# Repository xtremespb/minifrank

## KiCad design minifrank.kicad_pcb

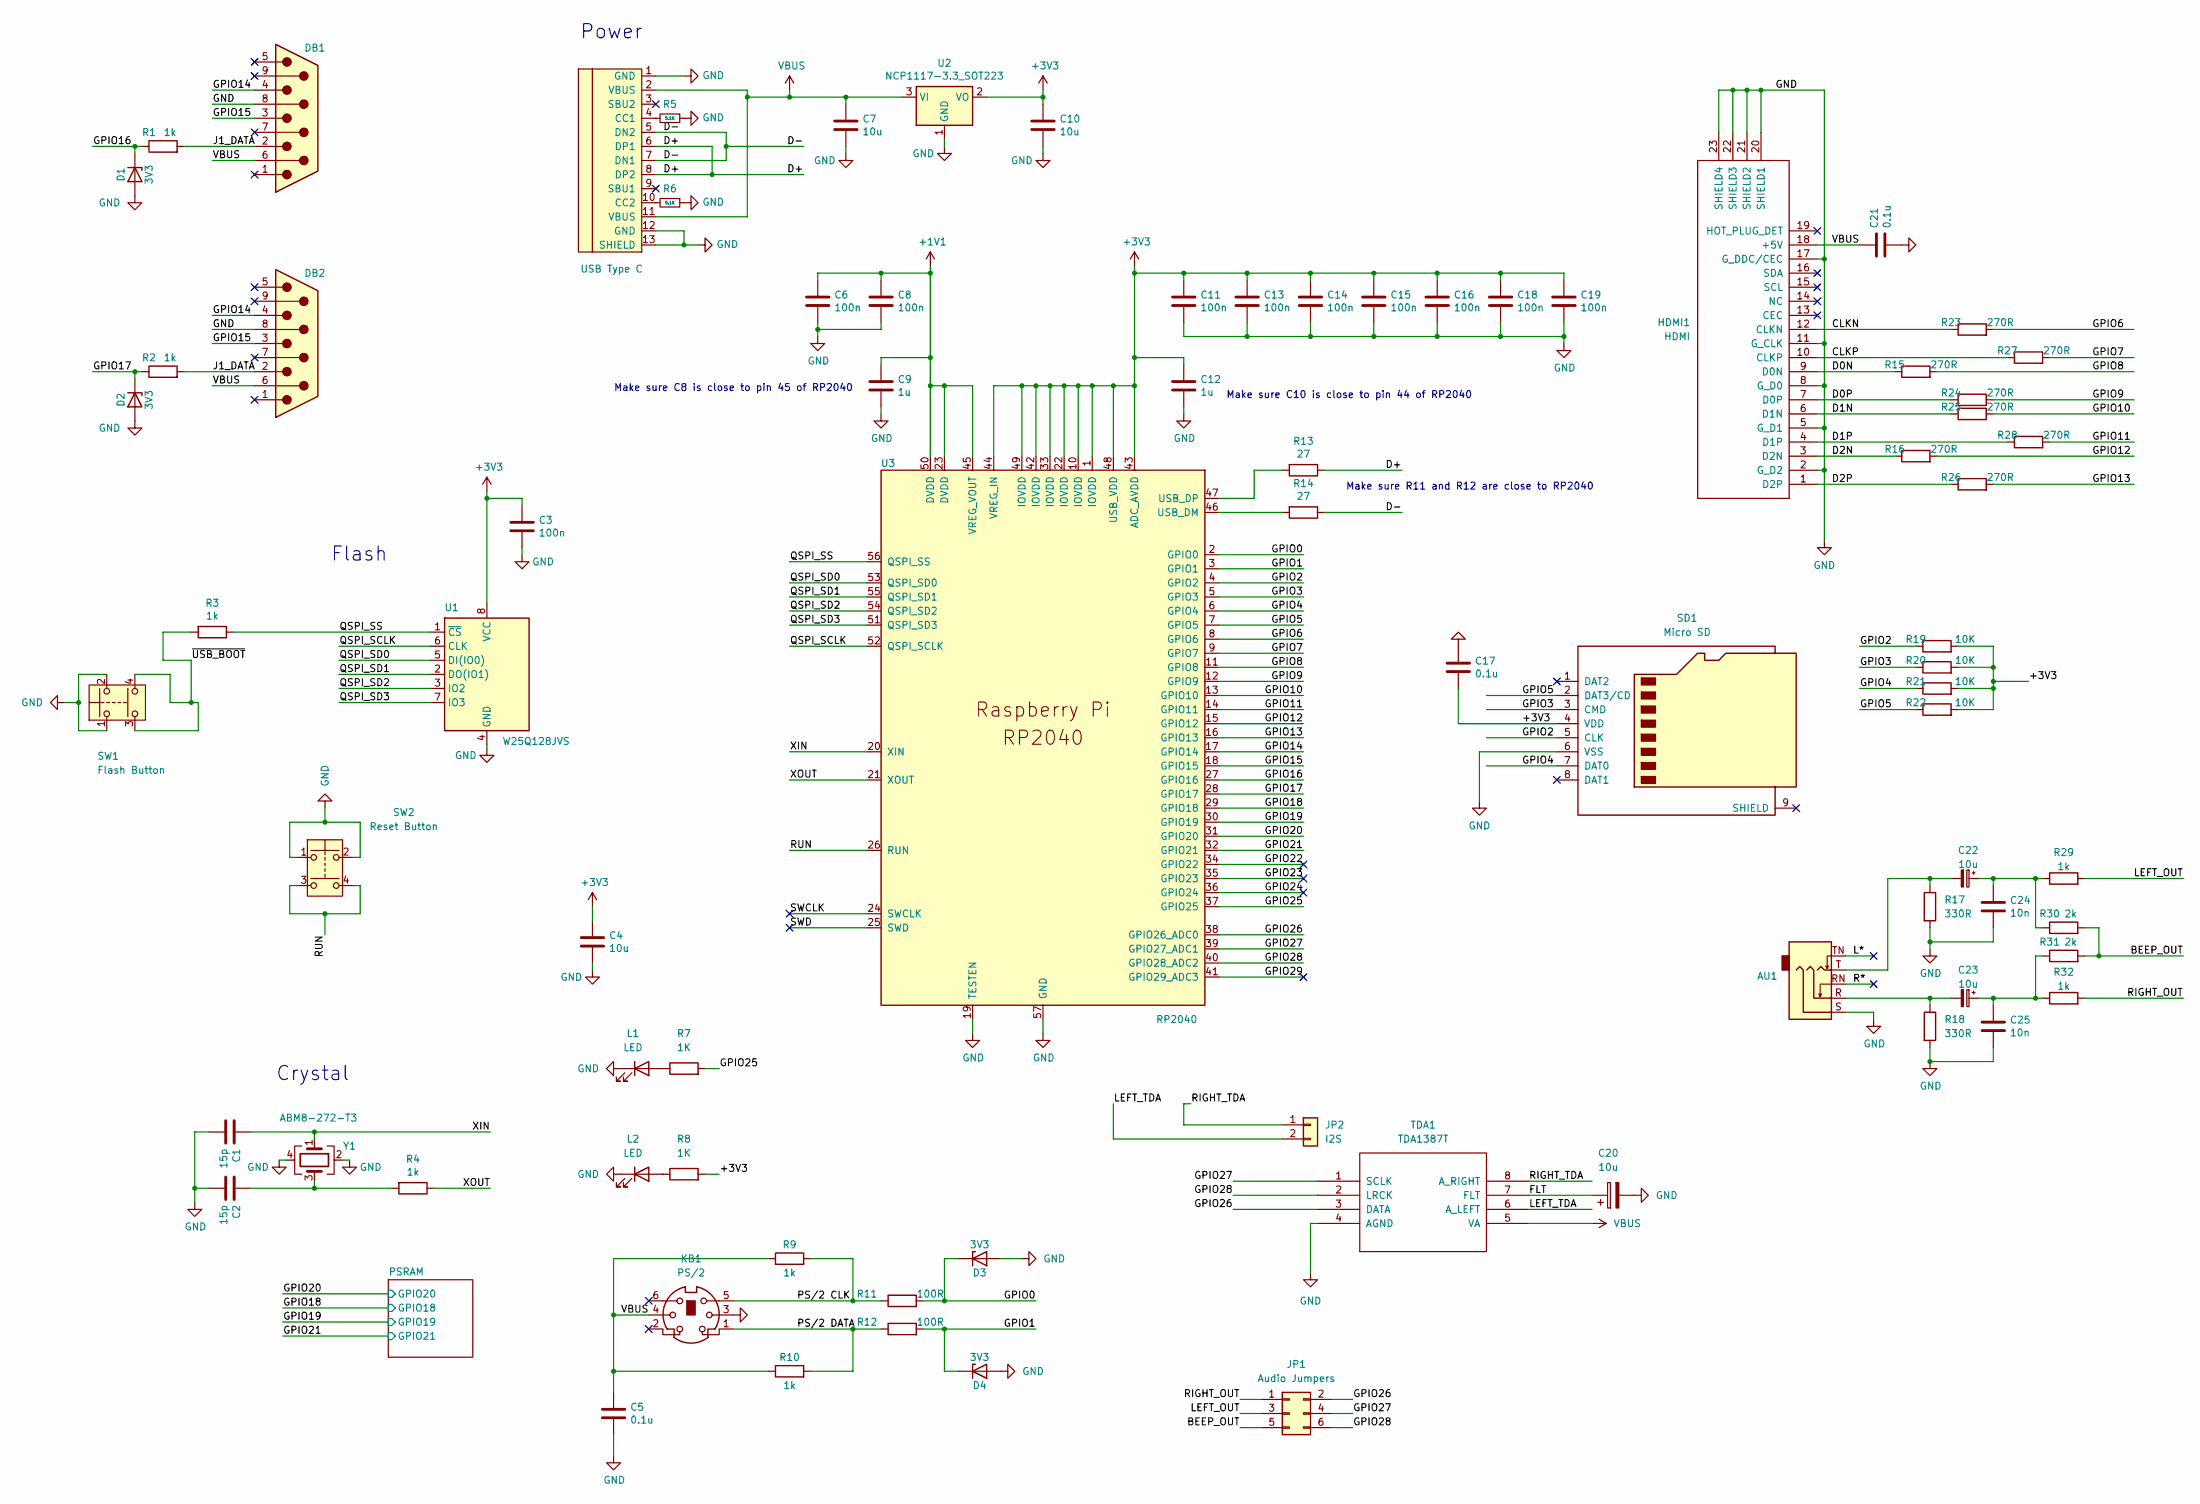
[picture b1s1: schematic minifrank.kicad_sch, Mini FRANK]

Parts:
AU1: AUDIO OUT; Medved_Jack_3.5mm_CUI_SJ1-3535NG_Horizontal
C1, C2: 15p; Medved_C_0805
C3, C6, C8, C11, C13, C14, C15, C16, C18, C19: 100n; Medved_C_0805
C4, C7, C10, C22, C23: 10u; Medved_C_0805
C5, C17, C21: 0.1u; Medved_C_0805
C9, C12: 1u; Medved_C_0805
C20: 10u; Medved_CP_Radial_D5.0mm_P2.50mm
C24, C25: 10n; Medved_C_0805
D1, D2, D3, D4: 3V3; Medved_D_0805
DB1, DB2: Joystick; DSUB-9_Male_EdgeMount_P2.77mm
HDMI1: HDMI
JP1: Audio Jumpers; Medved_JMP_2x03
JP2: I2S; Medved_PinHeader_1x02
KB1: PS/2; Connector_Mini-DIN_Female_6Pin_2rows
L1, L2: LED; LED_0805_2012Metric_Pad1.15x1.40mm_HandSolder
R1, R2, R3, R4, R9, R10, R29, R32: 1k; Medved_R_0805
R5, R6: 5.1K; Medved_R_0805
R7, R8: 1K; Medved_R_0805
R11, R12: 100R; Medved_R_0805
R13, R14: 27; Medved_R_0805
R15, R16, R23, R24, R25, R26, R27, R28: 270R; Medved_R_0805
R17, R18: 330R; Medved_R_0805
R19, R20, R21, R22: 10K; Medved_R_0805
R30, R31: 2k; Medved_R_0805
SD1: Micro SD; Medved_SD_Card
SW1: Flash Button; Button_SMD_3x3x2
SW2: Reset Button; Button_SMD_3x3x2
TDA1: TDA1387T; SO-8_5.3x6.2mm_P1.27mm
U1: W25Q128JVS; SOIC-8_5.23x5.23mm_P1.27mm
U2: NCP1117-3.3_SOT223; SOT-223-3_TabPin2
U3: RP2040; RP2040-QFN-56
USB1: USB Type C; USB-TYPE-C-31-M-12_lib2; LCSC C165948
Y1: ABM8-272-T3; Crystal_SMD_3225-4Pin_3.2x2.5mm

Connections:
+1V1: C6.1, C8.1, C9.1, U3.23 (DVDD), U3.45 (VREG_VOUT), U3.50 (DVDD)
+3V3: C3.1, C4.1, C10.1, C11.1, C12.1, C13.1, C14.1, C15.1, C16.1, C17.2, C18.1, C19.1, R8.2, R19.2, R20.2, R21.2, R22.2, SD1.4 (VDD), U1.8 (VCC), U2.2 (VO), U3.1 (IOVDD), U3.10 (IOVDD), U3.22 (IOVDD), U3.33 (IOVDD), U3.42 (IOVDD), U3.43 (ADC_AVDD), U3.44 (VREG_IN), U3.48 (USB_VDD), U3.49 (IOVDD); also elsewhere on the board
/BEEP_OUT: JP1.5, R30.2, R31.2
/CLKN: HDMI1.12 (CLKN), R23.1
/CLKP: HDMI1.10 (CLKP), R27.1
/D0N: HDMI1.9 (D0N), R15.1
/D0P: HDMI1.7 (D0P), R24.1
/D1N: HDMI1.6 (D1N), R25.1
/D1P: HDMI1.4 (D1P), R28.1
/D2N: HDMI1.3 (D2N), R16.1
/D2P: HDMI1.1 (D2P), R26.1
/D+: R13.1, USB1.6 (DP1), USB1.8 (DP2)
/D-: R14.1, USB1.5 (DN2), USB1.7 (DN1)
/FLT: C20.1, TDA1.7 (FLT)
/GPIO0: D3.1 (K), R11.2, U3.2 (GPIO0)
/GPIO1: D4.1 (K), R12.2, U3.3 (GPIO1)
/GPIO2: R19.1, SD1.5 (CLK), U3.4 (GPIO2)
/GPIO3: R20.1, SD1.3 (CMD), U3.5 (GPIO3)
/GPIO4: R21.1, SD1.7 (DAT0), U3.6 (GPIO4)
/GPIO5: R22.1, SD1.2 (DAT3/CD), U3.7 (GPIO5)
/GPIO6: R23.2, U3.8 (GPIO6)
/GPIO7: R27.2, U3.9 (GPIO7)
/GPIO8: R15.2, U3.11 (GPIO8)
/GPIO9: R24.2, U3.12 (GPIO9)
/GPIO10: R25.2, U3.13 (GPIO10)
/GPIO11: R28.2, U3.14 (GPIO11)
/GPIO12: R16.2, U3.15 (GPIO12)
/GPIO13: R26.2, U3.16 (GPIO13)
/GPIO14: DB1.4, DB2.4, U3.17 (GPIO14)
/GPIO15: DB1.3, DB2.3, U3.18 (GPIO15)
/GPIO16: D1.1 (K), R1.1, U3.27 (GPIO16)
/GPIO17: D2.1 (K), R2.1, U3.28 (GPIO17)
/GPIO18: U3.29 (GPIO18); also elsewhere on the board
/GPIO19: U3.30 (GPIO19); also elsewhere on the board
/GPIO20: U3.31 (GPIO20); also elsewhere on the board
/GPIO21: U3.32 (GPIO21); also elsewhere on the board
/GPIO22: U3.34 (GPIO22)
/GPIO23: U3.35 (GPIO23)
/GPIO24: U3.36 (GPIO24)
/GPIO25: R7.2, U3.37 (GPIO25)
/GPIO26: JP1.2, TDA1.3 (DATA), U3.38 (GPIO26_ADC0)
/GPIO27: JP1.4, TDA1.1 (SCLK), U3.39 (GPIO27_ADC1)
/GPIO28: JP1.6, TDA1.2 (LRCK), U3.40 (GPIO28_ADC2)
/GPIO29: U3.41 (GPIO29_ADC3)
/J1_DATA: DB1.2, DB2.2, R1.2, R2.2
/L*: AU1.TN
/LEFT_OUT: JP1.3, R29.2
/LEFT_TDA: JP2.2, TDA1.6 (A_LEFT)
/PS/2 CLK: KB1.5, R9.2, R11.1
/PS/2 DATA: KB1.1, R10.2, R12.1
/QSPI_SCLK: U1.6 (CLK), U3.52 (QSPI_SCLK)
/QSPI_SD0: U1.5 (DI(IO0)), U3.53 (QSPI_SD0)
/QSPI_SD1: U1.2 (DO(IO1)), U3.55 (QSPI_SD1)
/QSPI_SD2: U1.3 (IO2), U3.54 (QSPI_SD2)
/QSPI_SD3: U1.7 (IO3), U3.51 (QSPI_SD3)
/QSPI_SS: R3.1, U1.1 (~CS), U3.56 (QSPI_SS)
/R*: AU1.RN
/RIGHT_OUT: JP1.1, R32.2
/RIGHT_TDA: JP2.1, TDA1.8 (A_RIGHT)
/RUN: SW2.3, SW2.4, U3.26 (RUN)
/SWCLK: U3.24 (SWCLK)
/SWD: U3.25 (SWD)
/XIN: C1.1, U3.20 (XIN), Y1.1
/XOUT: R4.1, U3.21 (XOUT)
/~USB_BOOT: R3.2, SW1.3, SW1.4
GND: AU1.S, C1.2, C2.2, C3.2, C4.2, C5.2, C6.2, C7.2, C8.2, C9.2, C10.2, C11.2, C12.2, C13.2, C14.2, C15.2, C16.2, C17.1, C18.2, C19.2, C20.2, C21.2, C24.2, C25.2, D1.2 (A), D2.2 (A), D3.2 (A), D4.2 (A), DB1.8, DB2.8, HDMI1.2 (G_D2), HDMI1.5 (G_D1), HDMI1.8 (G_D0), HDMI1.11 (G_CLK), HDMI1.17 (G_DDC/CEC), HDMI1.20 (SHIELD1), HDMI1.21 (SHIELD2), HDMI1.22 (SHIELD3), HDMI1.23 (SHIELD4), KB1.3, L1.1 (K), L2.1 (K), R5.1, R6.1, R17.2, R18.2, SD1.6 (VSS), SW1.1, SW1.2, SW2.1, SW2.2, TDA1.4 (AGND), U1.4 (GND), U2.1 (GND), U3.19 (TESTEN), U3.57 (GND), USB1.1 (GND), USB1.12 (GND), USB1.13 (SHIELD), Y1.2, Y1.4; also elsewhere on the board
unnamed: AU1.R, C23.2, R18.1
unnamed: AU1.T, C22.2, R17.1
unnamed: C2.1, R4.2, Y1.3
unnamed: C22.1, C24.1, R29.1, R30.1
unnamed: C23.1, C25.1, R31.1, R32.1
unnamed: L1.2 (A), R7.1
unnamed: L2.2 (A), R8.1
unnamed: R14.2, U3.46 (USB_DM)
unnamed: R13.2, U3.47 (USB_DP)
unnamed: R5.2, USB1.4 (CC1)
unnamed: R6.2, USB1.10 (CC2)
VBUS: C5.1, C7.1, C21.1, DB1.6, DB2.6, HDMI1.18 (+5V), KB1.4, R9.1, R10.1, TDA1.5 (VA), U2.3 (VI), USB1.2 (VBUS), USB1.11 (VBUS)

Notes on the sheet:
Power
Crystal
Make sure C8 is close to pin 45 of RP2040
Make sure C10 is close to pin 44 of RP2040
Make sure R11 and R12 are close to RP2040
Flash

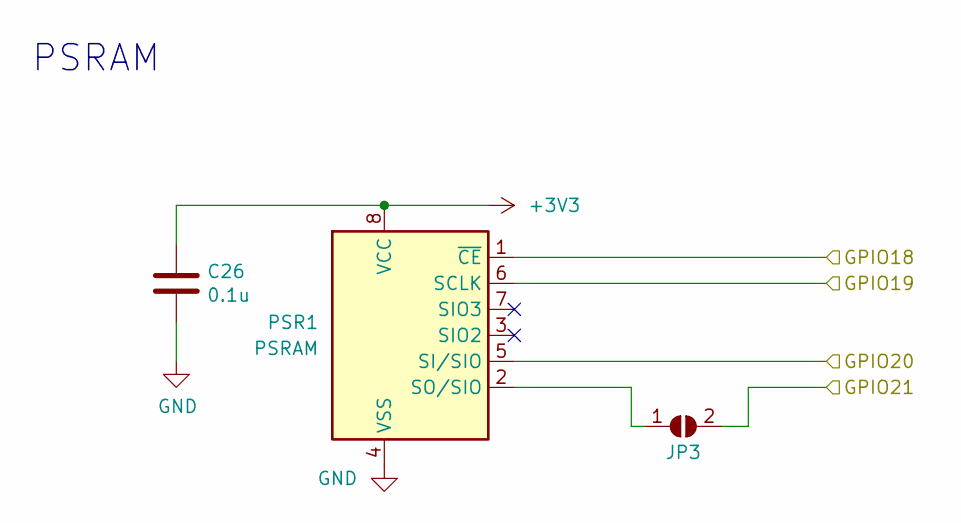
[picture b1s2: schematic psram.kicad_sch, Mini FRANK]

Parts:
C26: 0.1u; C_0805_2012Metric_Pad1.18x1.45mm_HandSolder
JP3: JMP PSRAM; SolderJumper-2_P1.3mm_Open_RoundedPad1.0x1.5mm
PSR1: PSRAM; SO-8_5.3x6.2mm_P1.27mm

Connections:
+3V3: C26.1, PSR1.8 (VCC); also elsewhere on the board
/GPIO18: PSR1.1 (~CE); also elsewhere on the board
/GPIO19: PSR1.6 (SCLK); also elsewhere on the board
/GPIO20: PSR1.5 (SI/SIO); also elsewhere on the board
/GPIO21: JP3.2 (B); also elsewhere on the board
GND: C26.2, PSR1.4 (VSS); also elsewhere on the board
unnamed: JP3.1 (A), PSR1.2 (SO/SIO)

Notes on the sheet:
PSRAM

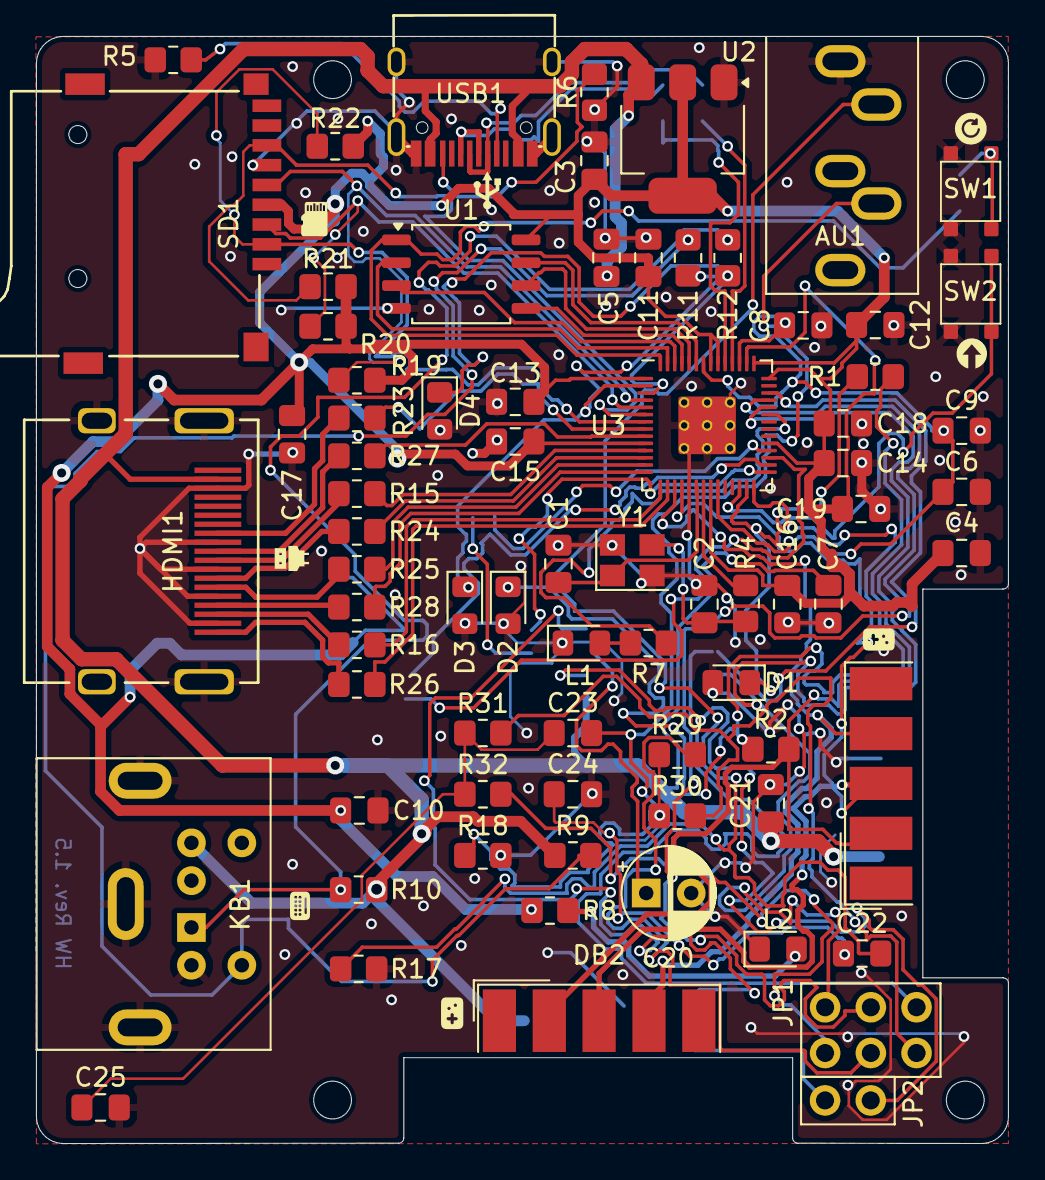
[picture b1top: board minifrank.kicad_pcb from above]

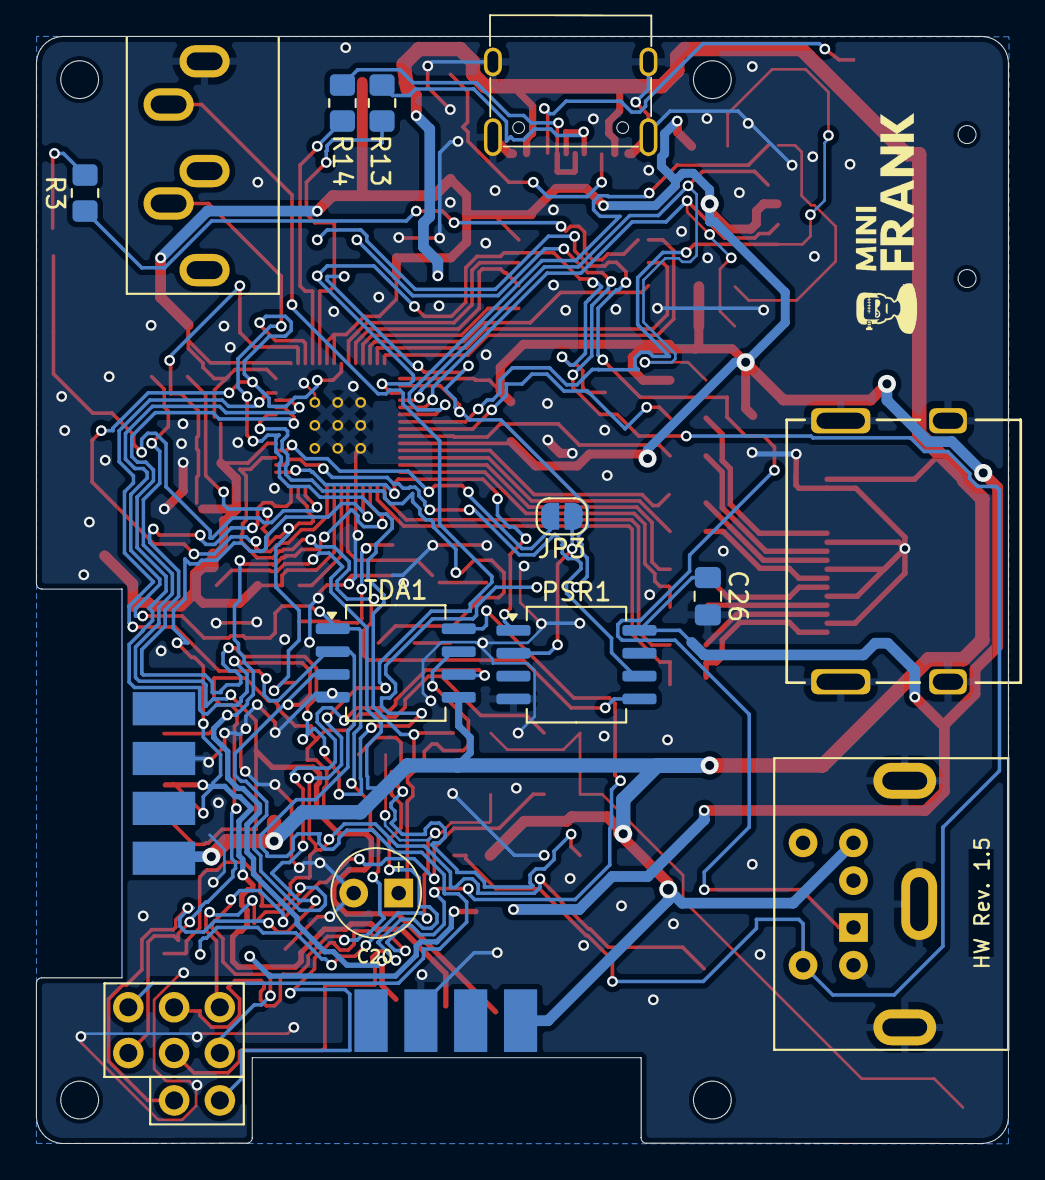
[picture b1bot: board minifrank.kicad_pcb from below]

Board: 2 copper layers, 54.0 x 61.5 mm, 82 parts (7 on the bottom side), 71 nets.

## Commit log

2024-09-17 Refactoring
2024-09-17 HW Rev 1.0
2024-09-17 HW Rev. 1.0 (final)
2024-09-17 Minor updates
2024-09-17 Minor fixes
2024-10-23 HW Rev 1.1
2024-11-13 HW Rev. 1.2
2024-11-27 HW Rev 1.3
2024-11-27 HW Rev 1.4
2024-11-28 Updates to HW Rev 1.4
2024-12-13 HW Rev 1.5
